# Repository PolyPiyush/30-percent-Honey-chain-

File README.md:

# 🍯 HoneyChain

### Blockchain-Based Honey Traceability & Smart Beekeeping System

> **From Hive to Consumer — Transparent, Traceable and Data-Driven Honey**

HoneyChain is a blockchain-based honey traceability and smart beekeeping platform designed to improve honey authenticity, supply-chain transparency, hive monitoring, and consumer trust.

The system combines **IoT, Artificial Intelligence, Blockchain, IPFS, Oracle services, REST APIs, PostgreSQL and QR-code authentication** into a unified framework connecting the journey of honey from the **beehive to the consumer**.

---

## 📌 Problem Statement

The honey industry faces several challenges:

- Counterfeit and adulterated honey
- Limited visibility into the origin of honey
- Fragmented supply-chain records
- Manual record keeping
- Limited monitoring of hive conditions
- Delayed detection of abnormal hive conditions
- Lack of transparent quality and certification records
- Difficulty for consumers to verify product history
- Limited access to data-driven decision support for beekeepers

---

## 💡 Our Solution

HoneyChain creates a **digital identity for honey batches** and connects that identity with information generated throughout the product lifecycle.

```text
SMART HIVE
    ↓
IoT MONITORING
    ↓
AI ANALYSIS
    ↓
HARVEST
    ↓
DIGITAL HONEY BATCH
    ↓
PROCESSING
    ↓
QUALITY TESTING
    ↓
CERTIFICATION
    ↓
BLOCKCHAIN TRACEABILITY
    ↓
DISTRIBUTION
    ↓
RETAIL
    ↓
QR VERIFICATION
    ↓
CONSUMER
```

> **The history of honey should begin at the hive and remain connected to the product until it reaches the consumer.**

---

## ✨ Key Features

### 🐝 Smart Hive Monitoring
IoT sensors can collect hive-related parameters such as temperature, humidity, weight and other environmental conditions.

### 🤖 AI-Based Analytics
Machine learning can support colony health monitoring, anomaly detection, productivity analysis and early-warning alerts.

### ⛓️ Blockchain Traceability
Critical supply-chain events are recorded on blockchain to provide tamper-evident provenance and verification.

### 📦 Digital Honey Batch
Each harvested honey lot receives a unique digital identity connected to its origin, processing, quality, certification and supply-chain history.

### 📁 IPFS Document Storage
Large supporting files such as laboratory reports, certificates, inspection documents and images can be stored off-chain using IPFS.

### 🔗 Oracle Integration
An oracle provides a controlled bridge between external systems/data and blockchain smart contracts.

### 📱 QR Consumer Verification
Consumers can scan a QR code to access the verified digital history of a honey batch.

---

## 🏗️ System Architecture

```text
                    ┌───────────────────────┐
                    │      SMART HIVE       │
                    │  IoT Sensors/Devices  │
                    └───────────┬───────────┘
                                │
                                ▼
                    ┌───────────────────────┐
                    │   IoT Communication   │
                    │     MQTT / REST       │
                    └───────────┬───────────┘
                                │
                                ▼
              ┌─────────────────────────────────┐
              │          BACKEND API             │
              │       NestJS / TypeScript       │
              └───────────────┬─────────────────┘
                              │
             ┌────────────────┼─────────────────┐
             │                │                 │
             ▼                ▼                 ▼
      ┌────────────┐   ┌─────────────┐   ┌─────────────┐
      │ PostgreSQL │   │ AI / ML     │   │    IPFS     │
      │  Database  │   │ Analytics   │   │  Documents  │
      └────────────┘   └─────────────┘   └─────────────┘
             │                │                 │
             └────────────────┼─────────────────┘
                              │
                              ▼
                    ┌───────────────────────┐
                    │       ORACLE          │
                    │ External Data Bridge  │
                    └───────────┬───────────┘
                                │
                                ▼
                    ┌───────────────────────┐
                    │       BLOCKCHAIN       │
                    │   Solidity Contracts   │
                    │   Polygon Amoy Testnet │
                    └───────────┬───────────┘
                                │
                                ▼
                    ┌───────────────────────┐
                    │     QR VERIFICATION   │
                    └───────────┬───────────┘
                                │
                                ▼
                    ┌───────────────────────┐
                    │       CONSUMER        │
                    └───────────────────────┘
```

---

## 🔄 Complete Workflow

```text
Hive Registration
      ↓
IoT Monitoring
      ↓
AI Analysis
      ↓
Honey Harvest
      ↓
Digital Batch Creation
      ↓
Processing
      ↓
Quality Testing
      ↓
Certification
      ↓
Blockchain Recording
      ↓
Supply-Chain Transfers
      ↓
QR Generation
      ↓
Consumer Verification
```

---

## ⛓️ Blockchain Layer

**Prototype Network:** Polygon Amoy Testnet  
**Smart Contracts:** Solidity  
**Development:** Hardhat  
**Blockchain Client:** ethers.js

Critical events can include:

- Batch creation
- Harvest recording
- Processing events
- Quality/certification references
- Ownership transfers
- Verification records
- IPFS document references

HoneyChain uses blockchain selectively rather than storing every sensor reading on-chain.

---

## 📡 IoT & Smart Hive

Possible monitored parameters include:

```text
Temperature
Humidity
Hive Weight
Acoustic Information
Environmental Conditions
```

Data flow:

```text
Sensors
   ↓
Microcontroller / Gateway
   ↓
MQTT / REST
   ↓
Backend API
   ↓
Database
   ↓
AI Analytics
```

---

## 🤖 AI & Machine Learning

A proposed model for structured hive-data classification is **Random Forest**.

Example input features:

```text
temperature
humidity
hive_weight
weight_change
time_of_day
historical_sensor_values
```

Example outputs:

```text
Normal
Warning
Anomalous
```

AI is intended as decision support and not as a replacement for professional beekeeping or laboratory diagnosis.

---

## 📁 IPFS

Large supporting documents can be stored using IPFS.

```text
Document
   ↓
IPFS
   ↓
CID
   ↓
Blockchain / Database Reference
```

This avoids putting entire files directly on blockchain and helps reduce storage requirements.

---

## 🔗 Oracle

The oracle layer provides a bridge between external systems and blockchain:

```text
External System
      ↓
Oracle
      ↓
Smart Contract
      ↓
Blockchain
```

Potential uses include selected IoT-derived events, verified quality information and external verification services.

---

## 📱 QR Code Verification

A QR code connects the physical product to its digital batch identity.

```text
Consumer
   ↓
QR Scan
   ↓
Batch ID / Verification URL
   ↓
Backend API
   ↓
Database + Blockchain + IPFS
   ↓
Traceability Page
```

The QR code does not need to contain the complete supply-chain history; it acts as the connection to the digital record.

---

## 🚚 Supply Chain

```text
BEEKEEPER
    ↓
PROCESSOR
    ↓
DISTRIBUTOR
    ↓
RETAILER
    ↓
CONSUMER
```

Transfers can validate the sender, receiver, batch, quantity, ownership, status, authorization and timestamp.

---

## 🔐 Backend Architecture

Proposed backend stack:

```text
NestJS
TypeScript
PostgreSQL
Prisma
JWT
Argon2 / bcrypt
Swagger / OpenAPI
Redis / BullMQ
```

Architecture:

```text
Frontend
   ↓
REST API
   ↓
Controllers
   ↓
Services
   ↓
Database / Blockchain / IPFS / AI
```

---

## 🗄️ Database

Potential entities include:

```text
User
Role
Apiary
Hive
Sensor
SensorReading
AIAnalysis
Alert
Harvest
HoneyBatch
BatchDocument
ProcessingRecord
QualityTest
Certification
SupplyChainEvent
Product
QRCode
BlockchainTransaction
IPFSFile
OracleData
Notification
AuditLog
```

---

## 🔐 Security

HoneyChain follows a layered security approach:

- JWT authentication
- Role-based access control
- Input validation
- HTTPS-ready APIs
- CORS configuration
- Security headers
- Rate limiting
- Secure password hashing
- Environment-based secrets
- File validation
- Audit logging
- Blockchain transaction verification
- Idempotent operations

### User Roles

```text
SUPER_ADMIN
ADMIN
BEEKEEPER
PROCESSOR
DISTRIBUTOR
RETAILER
INSPECTOR
CONSUMER
```

---

## 📂 Recommended Project Structure

```text
HoneyChain/
│
├── frontend/
├── backend/
├── blockchain/
├── ml/
├── iot/
├── docs/
├── docker-compose.yml
└── README.md
```

A more detailed structure can be organized as:

```text
backend/src/
├── auth/
├── users/
├── apiaries/
├── hives/
├── sensors/
├── harvest/
├── batches/
├── supply-chain/
├── blockchain/
├── ipfs/
├── oracle/
└── ai/
```

---

## ⚙️ Installation

### Prerequisites

```text
Node.js
npm
Git
PostgreSQL
Python
Docker
```

For blockchain development:

```text
Hardhat
Solidity
Polygon Amoy RPC
Wallet
```

### Clone Repository

```bash
git clone https://github.com/YOUR_USERNAME/HoneyChain.git
cd HoneyChain
```

### Install Backend

```bash
cd backend
npm install
```

### Install Frontend

```bash
cd ../frontend
npm install
```

### Install ML Dependencies

```bash
cd ../ml
pip install -r requirements.txt
```

---

## 🔑 Environment Variables

Create a `.env` file in the backend:

```env
NODE_ENV=development

PORT=3000

DATABASE_URL=postgresql://USER:PASSWORD@localhost:5432/honeychain

JWT_SECRET=your_jwt_secret
JWT_REFRESH_SECRET=your_refresh_secret

POLYGON_RPC_URL=your_polygon_amoy_rpc_url

BLOCKCHAIN_PRIVATE_KEY=your_private_key

CONTRACT_ADDRESS=your_deployed_contract_address

IPFS_API_URL=your_ipfs_api_url

IPFS_GATEWAY_URL=your_ipfs_gateway_url

ORACLE_API_URL=your_oracle_api_url
```

Never commit private keys, passwords or API keys to GitHub.

---

## ▶️ Running the Project

### Backend

```bash
cd backend
npm run start:dev
```

### Frontend

```bash
cd frontend
npm run dev
```

### Blockchain

```bash
cd blockchain
npm install
npx hardhat compile
npx hardhat test
```

Deployment example:

```bash
npx hardhat run scripts/deploy.ts --network polygonAmoy
```

---

## 🔌 API Overview

Example API structure:

```text
/api/v1/auth
/api/v1/users
/api/v1/apiaries
/api/v1/hives
/api/v1/sensors
/api/v1/harvests
/api/v1/batches
/api/v1/processing
/api/v1/quality
/api/v1/supply-chain
/api/v1/blockchain
/api/v1/ipfs
/api/v1/oracle
/api/v1/qr
/api/v1/analytics
```

Example verification endpoint:

```http
GET /api/v1/verify/:batchId
```

---

## 📦 Batch Lifecycle

```text
CREATED
   ↓
HARVESTED
   ↓
PROCESSING
   ↓
QUALITY_CHECK
   ↓
CERTIFIED
   ↓
PACKAGED
   ↓
IN_TRANSIT
   ↓
DISTRIBUTED
   ↓
RETAIL
   ↓
SOLD
```

Invalid state transitions should be rejected.

---

## 📈 Scalability

HoneyChain follows a **hybrid architecture**.

High-volume data remains off-chain:

```text
IoT Data
AI Data
Application Data
Large Documents
```

Critical traceability events are recorded on-chain:

```text
Batch Creation
Important Supply-Chain Events
Ownership Changes
Verification Records
Document References
```

Therefore, increasing the number of hives primarily increases database, API and analytics workloads rather than requiring every sensor reading to become a blockchain transaction.

The system can scale through:

- Horizontal API scaling
- Database indexing
- Redis caching
- Background queues
- Load balancing
- IPFS/object storage
- Containerized deployment
- Separate AI inference services

---

## 💰 Economic Feasibility

HoneyChain minimizes unnecessary blockchain costs through its hybrid design:

```text
High-volume data  → Database
Large documents   → IPFS
AI processing     → ML Service
Critical events   → Blockchain
Consumer access   → QR
```

This reduces unnecessary blockchain storage and transaction requirements while retaining verifiable traceability for important events.

QR codes and smartphone-based verification also provide a low-cost consumer interface.

---

## 🔬 Research Foundation

HoneyChain builds upon research in:

- Honey authenticity and laboratory analysis
- Precision apiculture
- IoT-based beehive monitoring
- Machine learning for hive monitoring
- Blockchain-based agricultural traceability
- Decentralized document storage
- Smart beehive architecture

### Research Gap

Existing research generally addresses IoT monitoring, AI analytics, honey authenticity, blockchain traceability and consumer verification as separate areas.

HoneyChain integrates these technologies into a unified framework connecting:

```text
Hive
 ↓
IoT
 ↓
AI
 ↓
Harvest
 ↓
Honey Batch
 ↓
Quality
 ↓
Blockchain
 ↓
Supply Chain
 ↓
QR
 ↓
Consumer
```

The contribution is primarily the **integration and application of these technologies to end-to-end honey traceability and smart beekeeping**.

---

## 🧪 Testing Strategy

HoneyChain can be validated through:

```text
Unit Testing
      ↓
API Testing
      ↓
Database Testing
      ↓
Smart Contract Testing
      ↓
Integration Testing
      ↓
QR Verification Testing
      ↓
End-to-End Testing
```

A complete test flow should cover:

```text
Beekeeper Registration
        ↓
Hive Registration
        ↓
IoT Data
        ↓
AI Analysis
        ↓
Harvest
        ↓
Batch Creation
        ↓
IPFS Document
        ↓
Blockchain Record
        ↓
Processing
        ↓
Quality Verification
        ↓
Supply Chain Transfer
        ↓
QR Generation
        ↓
Consumer Verification
```

---

## ⚠️ Limitations

### Blockchain
Blockchain makes recorded information tamper-evident but does not automatically guarantee that the original physical information was truthful.

### Honey Authenticity
Chemical authenticity still requires appropriate laboratory testing.

### AI
AI predictions depend on the quality, quantity and representativeness of training data.

### IoT
Sensor accuracy, connectivity and hardware reliability affect collected data.

### Prototype Environment
A testnet prototype does not represent all operating conditions of a production-scale national deployment.

---

## 🚀 Future Scope

- Real-world IoT hardware deployment
- Larger and geographically diverse datasets
- Improved ML models
- Computer-vision-based bee monitoring
- Edge AI
- Automated disease/anomaly detection
- Mobile application
- Multi-language consumer verification
- Laboratory-system integration
- Government certification integration
- Advanced analytics dashboards
- Production blockchain deployment
- Multi-region supply-chain deployment
- Extension to additional agricultural products

---

## 📚 References

```text
[1] Tsagkaris, A. S. et al. (2021). Honey authenticity: analytical techniques, state of the art and challenges. RSC Advances, 11, 11273–11294.

[2] Henry, M. et al. (2019). Precision apiculture: Development of a wireless sensor network for honeybee hives. Computers and Electronics in Agriculture, 156, 138–144.

[3] Tashakkori, R., Hamza, A. B. & Crawford, J. (2021). Beemon: An IoT-based beehive monitoring system. Computers and Electronics in Agriculture, 190, 106427.

[4] Salah, K. et al. (2019). Blockchain-Based Soybean Traceability in Agricultural Supply Chain. IEEE Access, 7, 73295–73305.

[5] Kamble, S. S., Gunasekaran, A. & Sharma, R. (2020). Modeling the blockchain enabled traceability in agriculture supply chain. International Journal of Information Management, 52, 101967.

[6] Hadjur, H., Ammar, D. & Lefèvre, L. (2022). Toward an intelligent and efficient beehive: A survey of precision beekeeping systems and services. Computers and Electronics in Agriculture, 192, 106604.

[7] Aydin, A. & Aydin, M. (2022). Design and implementation of a smart beehive and its monitoring system using microservices in the context of IoT and open data. Computers and Electronics in Agriculture, 196, 106897.

[8] Bilik, S. et al. (2024). Machine learning and computer vision techniques in continuous beehive monitoring applications: A survey. Computers and Electronics in Agriculture, 217, 108560.
```

---

## 👥 Contributors

**HoneyChain Team — SIH 2026**

**Domain:** Agriculture / Blockchain / IoT / AI  
**Focus:** Honey Traceability & Smart Beekeeping

---

## 📜 License

This project is developed as a prototype for **Smart India Hackathon 2026**.

Add an appropriate open-source license if the repository is intended for public reuse.

---

# 🍯 HoneyChain

### **Smart Hive → Intelligent Monitoring → Digital Batch → Blockchain Traceability → QR Verification → Consumer Trust**

> **From Hive to Consumer, Every Batch Has a Story.**

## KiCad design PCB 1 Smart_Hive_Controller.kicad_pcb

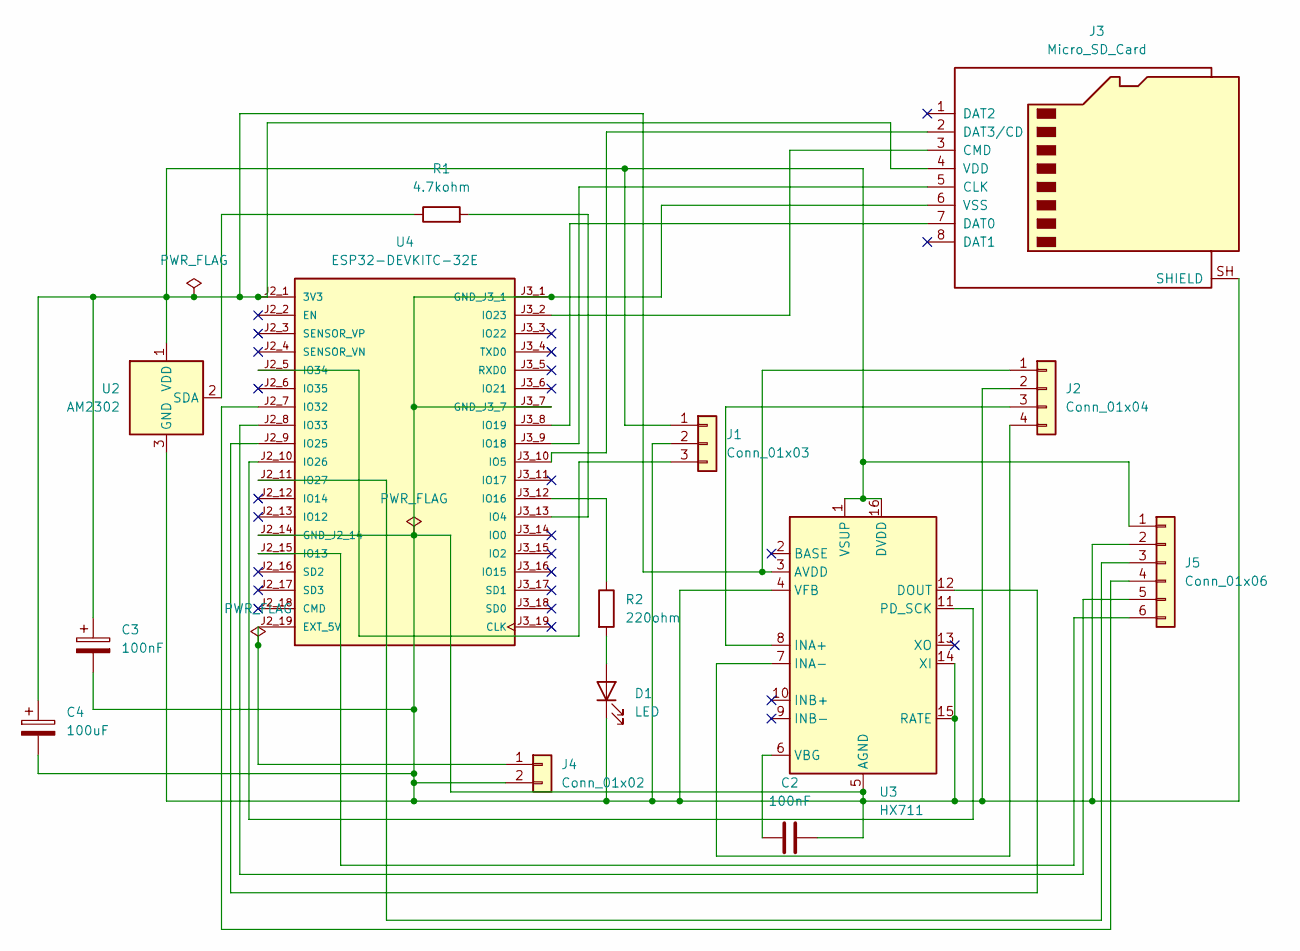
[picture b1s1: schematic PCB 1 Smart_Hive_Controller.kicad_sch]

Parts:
C2, C3: 100nF; C_Disc_D5.0mm_W2.5mm_P5.00mm
C4: 100uF; CP_Radial_D5.0mm_P2.00mm
D1: LED; LED_D5.0mm
J1: Conn_01x03; PinHeader_1x03_P2.54mm_Vertical
J2: Conn_01x04; PinHeader_1x04_P2.54mm_Vertical
J3: Micro_SD_Card; microSD_HC_Molex_104031-0811
J4: Conn_01x02; PinHeader_1x02_P2.54mm_Vertical
J5: Conn_01x06; PinHeader_1x06_P2.54mm_Vertical
R1: 4.7kohm; R_Axial_DIN0207_L6.3mm_D2.5mm_P10.16mm_Horizontal
R2: 220ohm; R_Axial_DIN0207_L6.3mm_D2.5mm_P10.16mm_Horizontal
U2: AM2302; PinHeader_1x03_P2.54mm_Vertical
U3: HX711; SOIC-16_3.9x9.9mm_P1.27mm
U4: ESP32-DEVKITC-32E; MODULE_ESP32-DEVKITC-32E; PARTREV 1.4

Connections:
unnamed: D1.2 (A), R2.2
unnamed: C3.1, C4.1, J1.1, J2.1, J3.4 (VDD), J5.1, U2.1 (VDD), U3.1 (VSUP), U3.3 (AVDD), U3.16 (DVDD), U4.J2_1 (3V3)
unnamed: J1.3, U4.J2_5 (IO34)
unnamed: J2.3, U3.8 (INA+)
unnamed: J2.4, U3.7 (INA-)
unnamed: J3.5 (CLK), U4.J3_9 (IO18)
unnamed: J3.3 (CMD), U4.J3_2 (IO23)
unnamed: J3.7 (DAT0), U4.J3_8 (IO19)
unnamed: J3.2 (DAT3/CD), U4.J3_10 (IO5)
unnamed: J4.1, U4.J2_19 (EXT_5V)
unnamed: J5.3, U4.J2_11 (IO27)
unnamed: J5.4, U4.J2_7 (IO32)
unnamed: J5.5, U4.J2_8 (IO33)
unnamed: J5.6, U4.J2_15 (IO13)
unnamed: R1.1, U2.2 (SDA)
unnamed: U3.12 (DOUT), U4.J2_9 (IO25)
unnamed: U3.11 (PD_SCK), U4.J2_10 (IO26)
unnamed: C2.1, U3.6 (VBG)
unnamed: R1.2, U4.J3_13 (IO4)
unnamed: R2.1, U4.J3_12 (IO16)

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
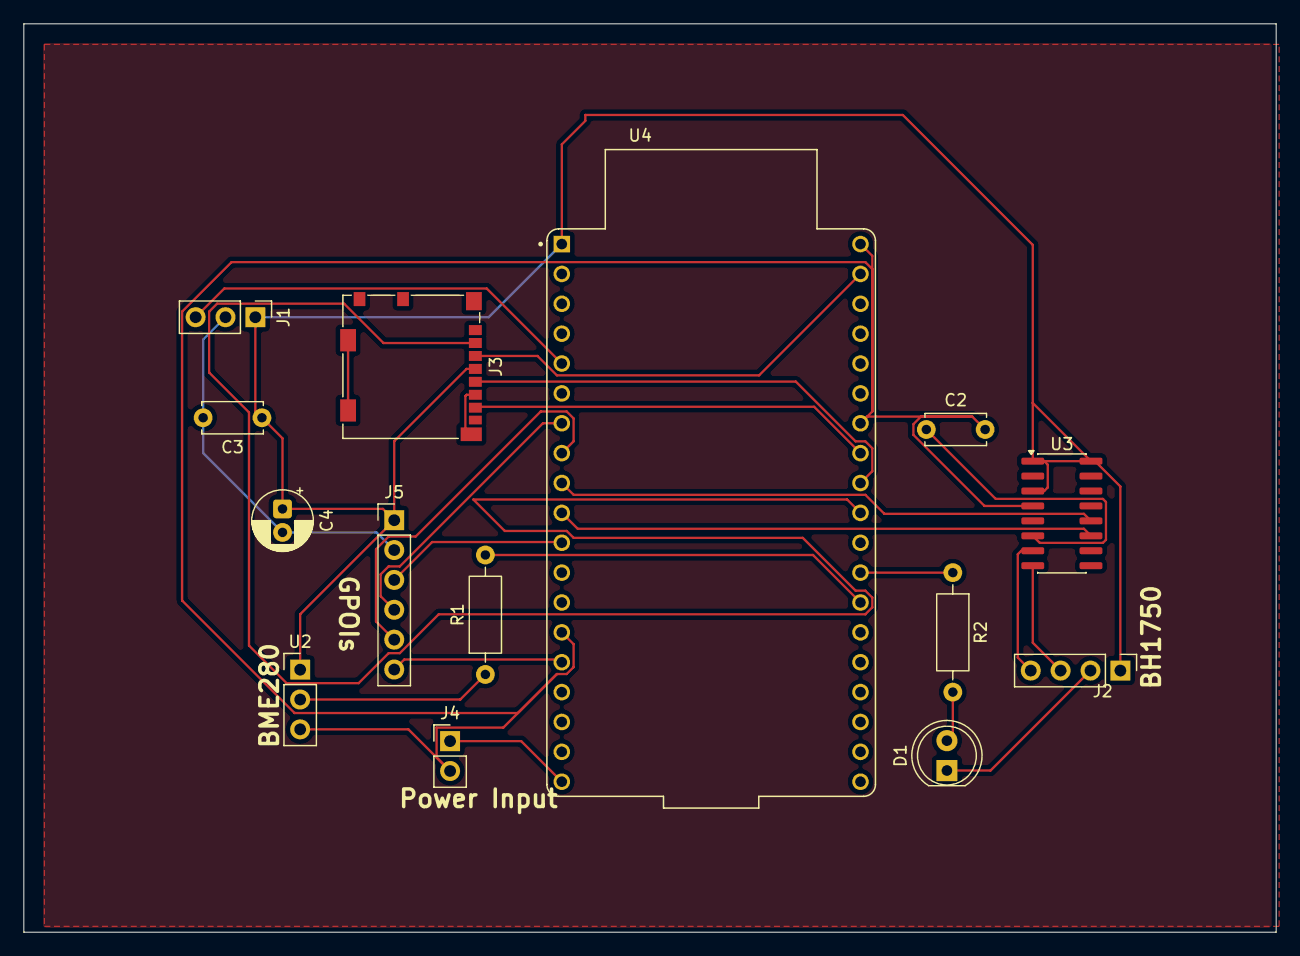
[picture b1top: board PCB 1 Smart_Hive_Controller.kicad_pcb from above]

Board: 2 copper layers, 106.5 x 77.2 mm, 14 parts (0 on the bottom side), 21 nets.

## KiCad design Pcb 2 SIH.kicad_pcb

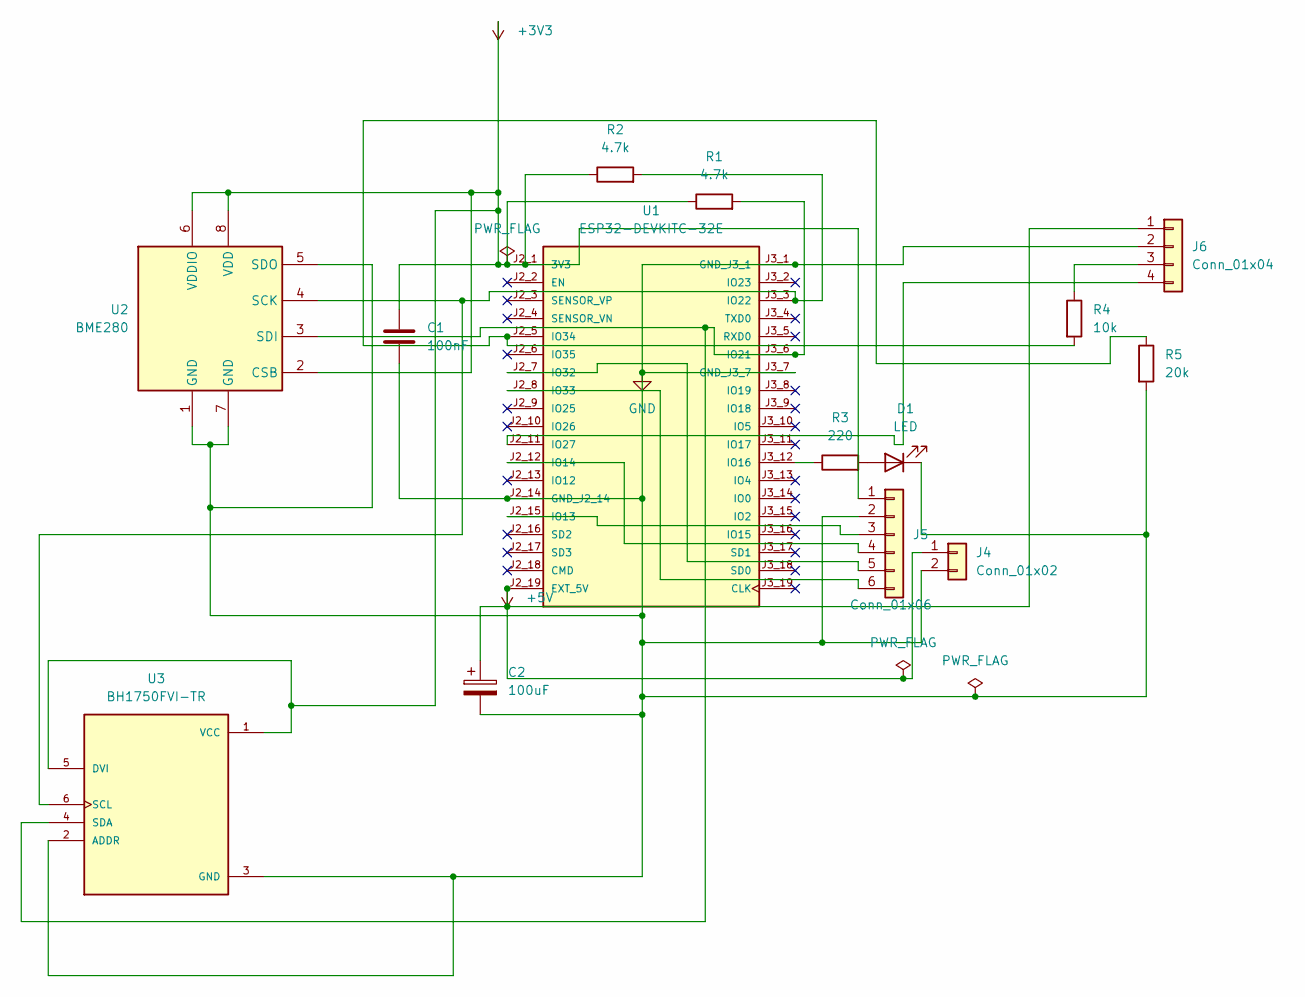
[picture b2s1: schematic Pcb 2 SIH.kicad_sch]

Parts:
C1: 100nF; C_Disc_D5.0mm_W2.5mm_P5.00mm
C2: 100uF; CP_Radial_D5.0mm_P2.00mm
D1: LED; LED_D5.0mm
J4: Conn_01x02; PinHeader_1x02_P2.54mm_Vertical
J5: Conn_01x06; PinHeader_1x06_P2.54mm_Vertical
J6: Conn_01x04; PinHeader_1x04_P2.54mm_Vertical
R1, R2: 4.7k; R_Axial_DIN0207_L6.3mm_D2.5mm_P10.16mm_Horizontal
R3: 220; R_Axial_DIN0207_L6.3mm_D2.5mm_P10.16mm_Horizontal
R4: 10k; R_Axial_DIN0207_L6.3mm_D2.5mm_P10.16mm_Horizontal
R5: 20k; R_Axial_DIN0207_L6.3mm_D2.5mm_P10.16mm_Horizontal
U1: ESP32-DEVKITC-32E; MODULE_ESP32-DEVKITC-32E; PARTREV 1.4
U2: BME280; LGA-12_2x2mm_P0.5mm
U3: BH1750FVI-TR; XDCR_BH1750FVI-TR; PARTREV D

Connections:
+3V3: C1.1, J5.1, R1.1, R2.1, U1.J2_1 (3V3), U2.2 (CSB), U2.6 (VDDIO), U2.8 (VDD), U3.1 (VCC), U3.5 (DVI)
+5V: C2.1, J4.1, J6.1, U1.J2_19 (EXT_5V)
GND: C1.2, C2.2, D1.1 (K), J4.2, J5.2, J6.2, R5.2, U1.J2_14 (GND_J2_14), U1.J3_1 (GND_J3_1), U1.J3_7 (GND_J3_7), U2.1 (GND), U2.5 (SDO), U2.7 (GND), U3.2 (ADDR), U3.3 (GND)
unnamed: D1.2 (A), R3.2
unnamed: J5.3, U1.J2_15 (IO13)
unnamed: J5.4, U1.J2_12 (IO14)
unnamed: J5.5, U1.J2_7 (IO32)
unnamed: J5.6, U1.J2_8 (IO33)
unnamed: J6.3, R4.1
unnamed: J6.4, U1.J2_11 (IO27)
unnamed: R3.1, U1.J3_12 (IO16)
unnamed: R1.2, U1.J3_6 (IO21), U2.3 (SDI), U3.4 (SDA)
unnamed: R2.2, U1.J3_3 (IO22), U2.4 (SCK), U3.6 (SCL)
unnamed: R4.2, R5.1, U1.J2_5 (IO34)

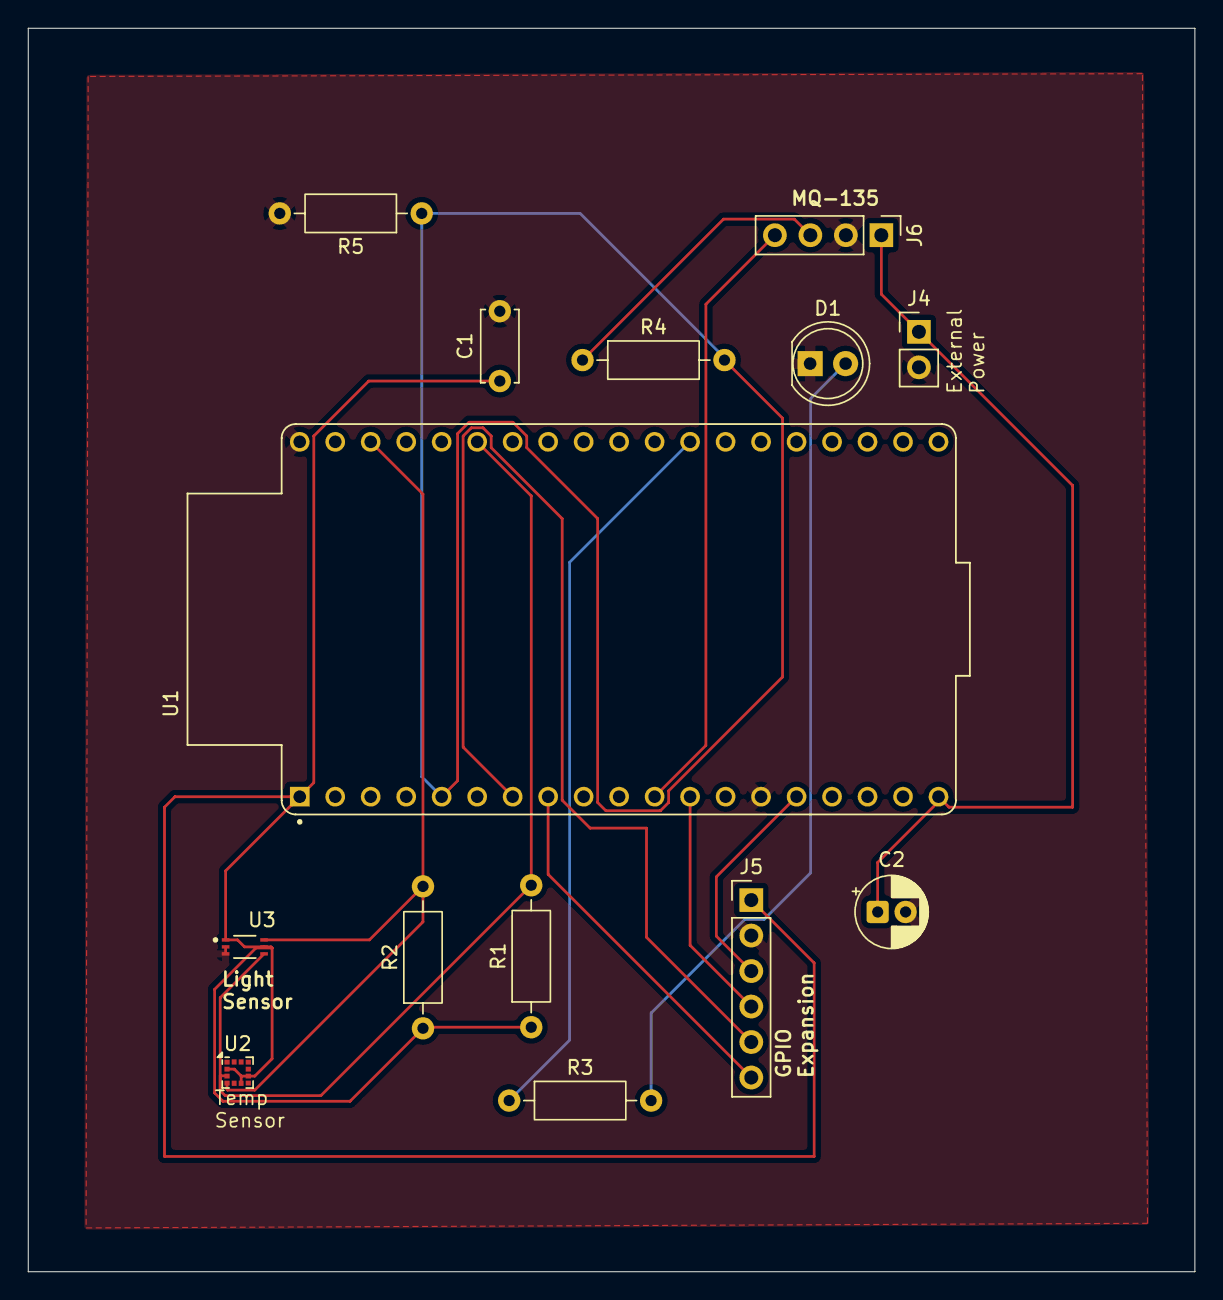
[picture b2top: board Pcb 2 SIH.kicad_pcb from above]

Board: 2 copper layers, 83.5 x 89.0 mm, 14 parts (0 on the bottom side), 14 nets.
